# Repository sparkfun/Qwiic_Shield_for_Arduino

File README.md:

SparkFun Qwiic Shield for Arduino
========================================

[*SparkFun Qwiic Shield (DEV-14352)*](https://www.sparkfun.com/products/14352)

An Arduino shield to connect the I<sup>2</sup>C bus to 4 Qwiic connect ports.

Repository Contents
-------------------

* **/Hardware** - Eagle design files (.brd, .sch)

Documentation
--------------

* **[Hookup Guide](https://learn.sparkfun.com/tutorials/qwiic-shield-for-arduino--photon-hookup-guide)** - Basic hookup guide for the Arduino Qwiic Shield
* **[SparkFun Fritzing repo](https://github.com/sparkfun/Fritzing_Parts)** - Fritzing diagrams for SparkFun products.
* **[SparkFun 3D Model repo](https://github.com/sparkfun/3D_Models)** - 3D models of SparkFun products. 
* **[SparkFun Graphical Datasheets](https://github.com/sparkfun/Graphical_Datasheets)** -Graphical Datasheets for various SparkFun products.

Product Versions
----------------
* [DEV-14352](https://www.sparkfun.com/products/14352)- An Arduino shield to connect the I<sup>2</sup>C bus to 4 Qwiic connect ports.

Version History
---------------
* [V1.0.0](https://github.com/sparkfun/Qwiic_Shield_for_Arduino/releases/tag/V_1.0.0) - Initial Release

License Information
-------------------

This product is _**open source**_! 

Please review the LICENSE.md file for license information. 

If you have any questions or concerns on licensing, please contact techsupport@sparkfun.com.

Distributed as-is; no warranty is given.

- Your friends at SparkFun.

_<COLLABORATION CREDIT>_

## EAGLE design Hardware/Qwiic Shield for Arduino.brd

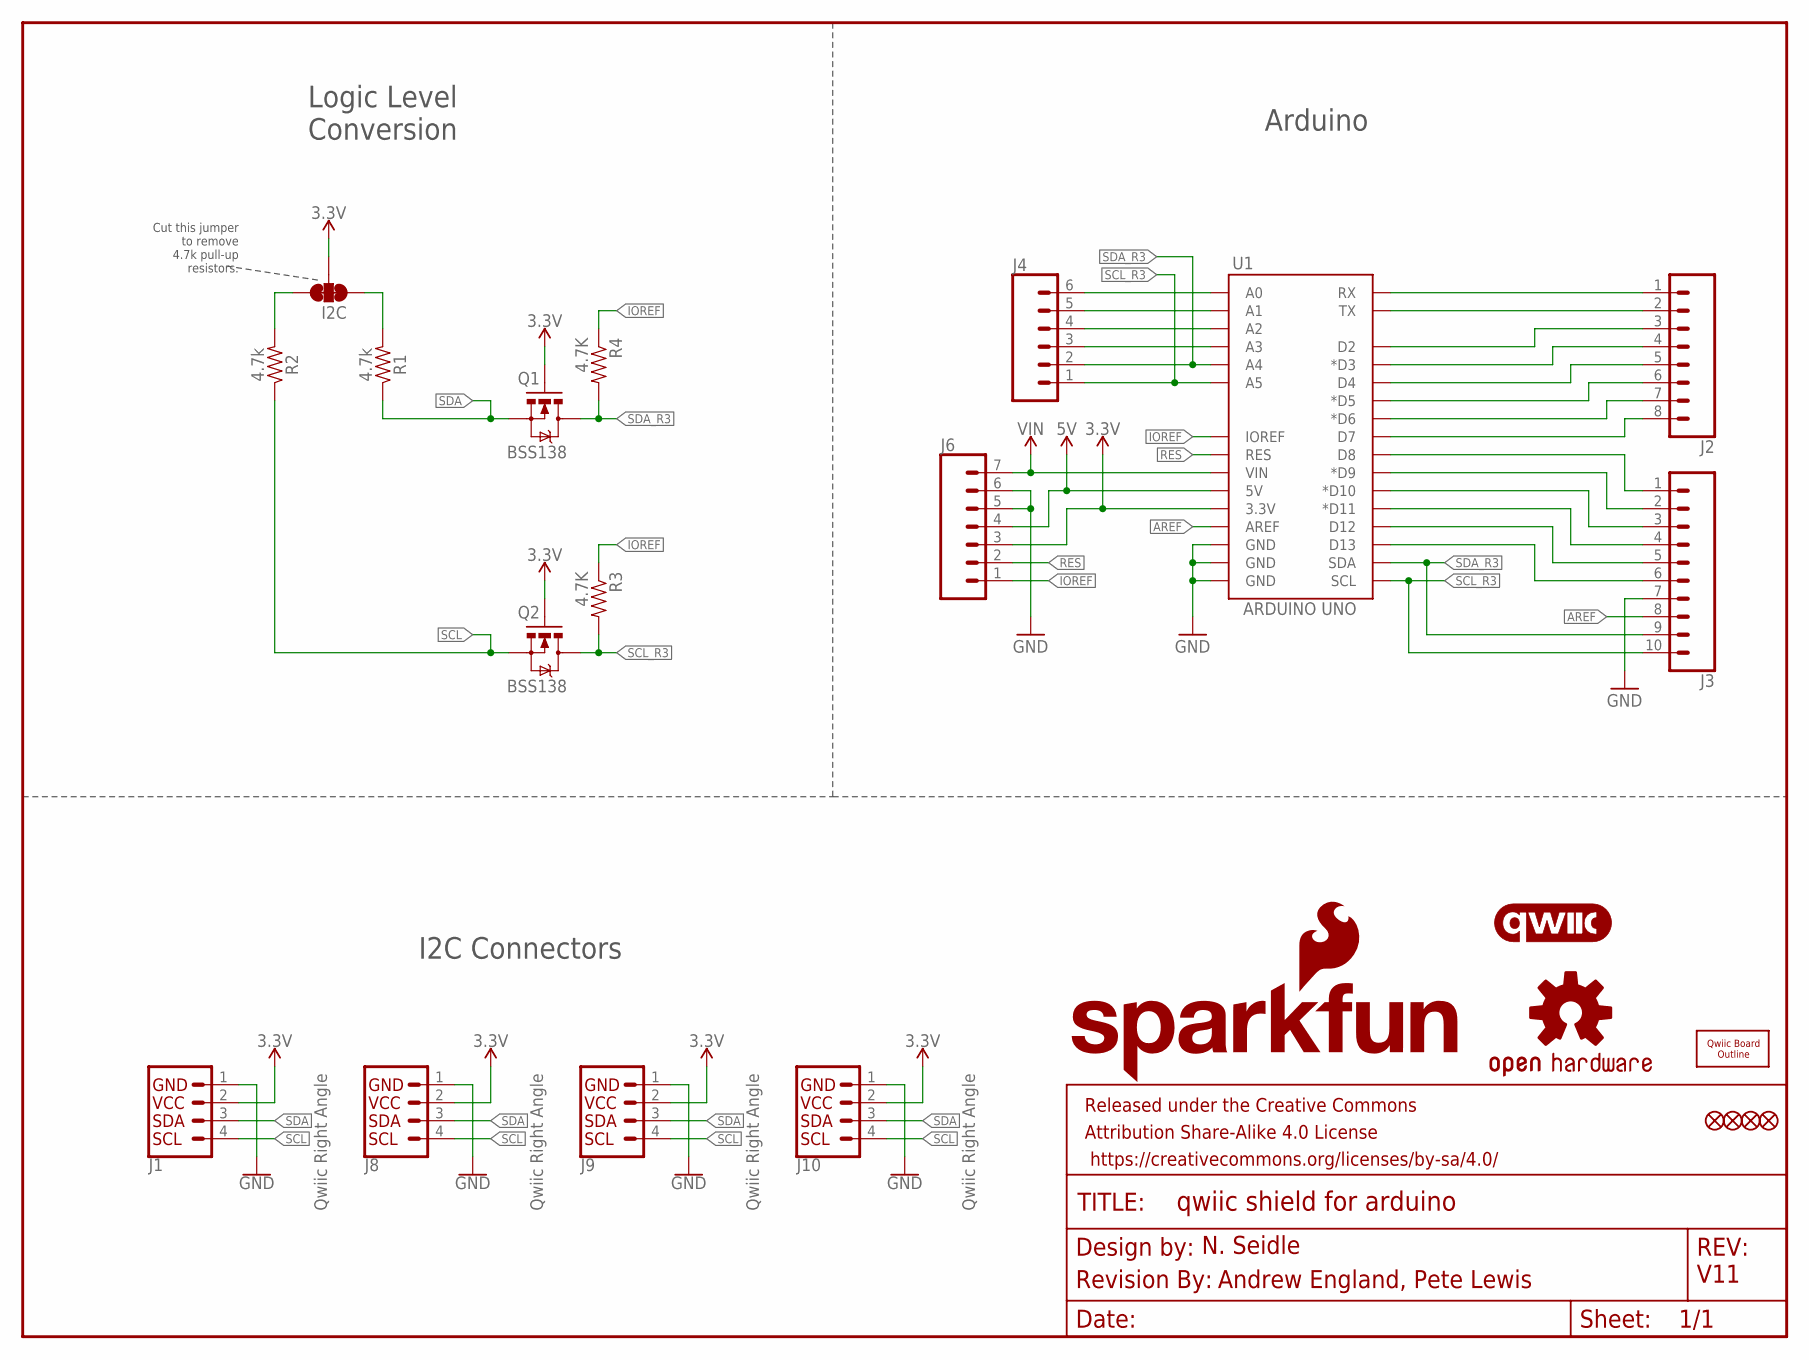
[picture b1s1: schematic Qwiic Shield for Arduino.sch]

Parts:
FD1, FD2, FD3, FD4: FIDUCIAL1X2; FIDUCIAL-1X2
FRAME1: FRAME-LETTER; CREATIVE_COMMONS
I2C: JUMPER-SMT_3_2-NC_TRACE_SILK; SMT-JUMPER_3_2-NC_TRACE_SILK
J1, J8, J9, J10: Qwiic Right Angle; 1X04_1MM_RA
J2: CONN_08NO_SILK_FEMALE_PTH; 1X08_NO_SILK
J3: CONN_10NO_SILK_PTH_FEMALE; 1X10_NO_SILK
J4: CONN_06NO_SILK_FEMALE_PTH; 1X06_NO_SILK
J6: CONN_07NO_SILK; 1X07_NO_SILK
LOGO1: OSHW-LOGOMINI; OSHW-LOGO-MINI
LOGO2: REVISION
LOGO3: QWIIC_LOGO_6MM; QWIIC_6MM
Q1, Q2: BSS138; SOT23-3
R1, R2: 4.7k; 0603
R3, R4: 4.7K; 0603-RES
U1: ARDUINO UNO; UNO_R3_SHIELD_NOLABELS
U$2: SFE_LOGO_NAME_FLAME.1_INCH; SFE_LOGO_NAME_FLAME_.1
U$3: QWIIC_BOARD_OUTLINEH; QWIIC_BOARD_MOUNT_HOLES

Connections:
3.3V: I2C.2, J1.2, J6.3, J8.2, J9.2, J10.2, Q1.1 (G), Q2.1 (G), U1.3.3V
5V: J6.4, U1.5V
A0: J4.6, U1.A0
A1: J4.5, U1.A1
A2: J4.4, U1.A2
A3: J4.3, U1.A3
AREF: J3.8, U1.AREF
D2: J2.3, U1.D2
D3: J2.4, U1.D3 (*D3)
D4: J2.5, U1.D4
D5: J2.6, U1.D5 (*D5)
D6: J2.7, U1.D6 (*D6)
D7: J2.8, U1.D7
D8: J3.1, U1.D8
D9: J3.2, U1.D9 (*D9)
D10: J3.3, U1.D10 (*D10)
D11: J3.4, U1.D11 (*D11)
D12: J3.5, U1.D12
D13: J3.6, U1.D13
GND: J1.1, J3.7, J6.5, J6.6, J8.1, J9.1, J10.1, U1.GND@0 (GND), U1.GND@1 (GND), U1.GND@2 (GND)
IOREF: J6.1, R3.1, R4.1, U1.IOREF
unnamed: I2C.3, R1.2
unnamed: I2C.1, R2.2
RES: J6.2, U1.RES
RX: J2.1, U1.RX
SCL: J1.4, J8.4, J9.4, J10.4, Q2.2 (S), R2.1
SCL_R3: J3.10, J4.1, Q2.3 (D), R3.2, U1.A5, U1.SCL
SDA: J1.3, J8.3, J9.3, J10.3, Q1.2 (S), R1.1
SDA_R3: J3.9, J4.2, Q1.3 (D), R4.2, U1.A4, U1.SDA
TX: J2.2, U1.TX
VIN: J6.7, U1.VIN

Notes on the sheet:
N. Seidle
Logic Level Conversion
Arduino
V11
I2C Connectors
Andrew England, Pete Lewis
Cut this jumper to remove 4.7k pull-up resistors.

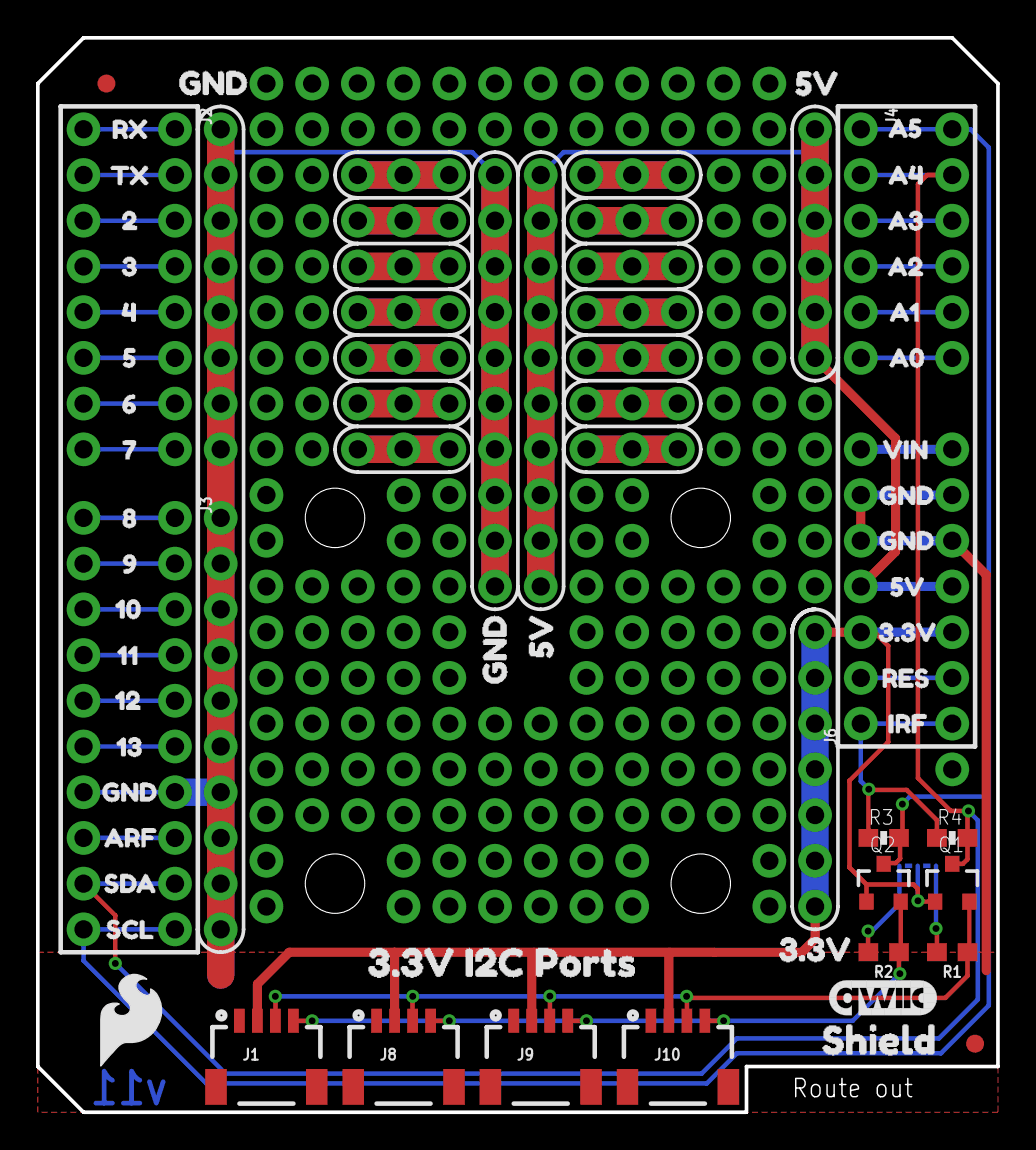
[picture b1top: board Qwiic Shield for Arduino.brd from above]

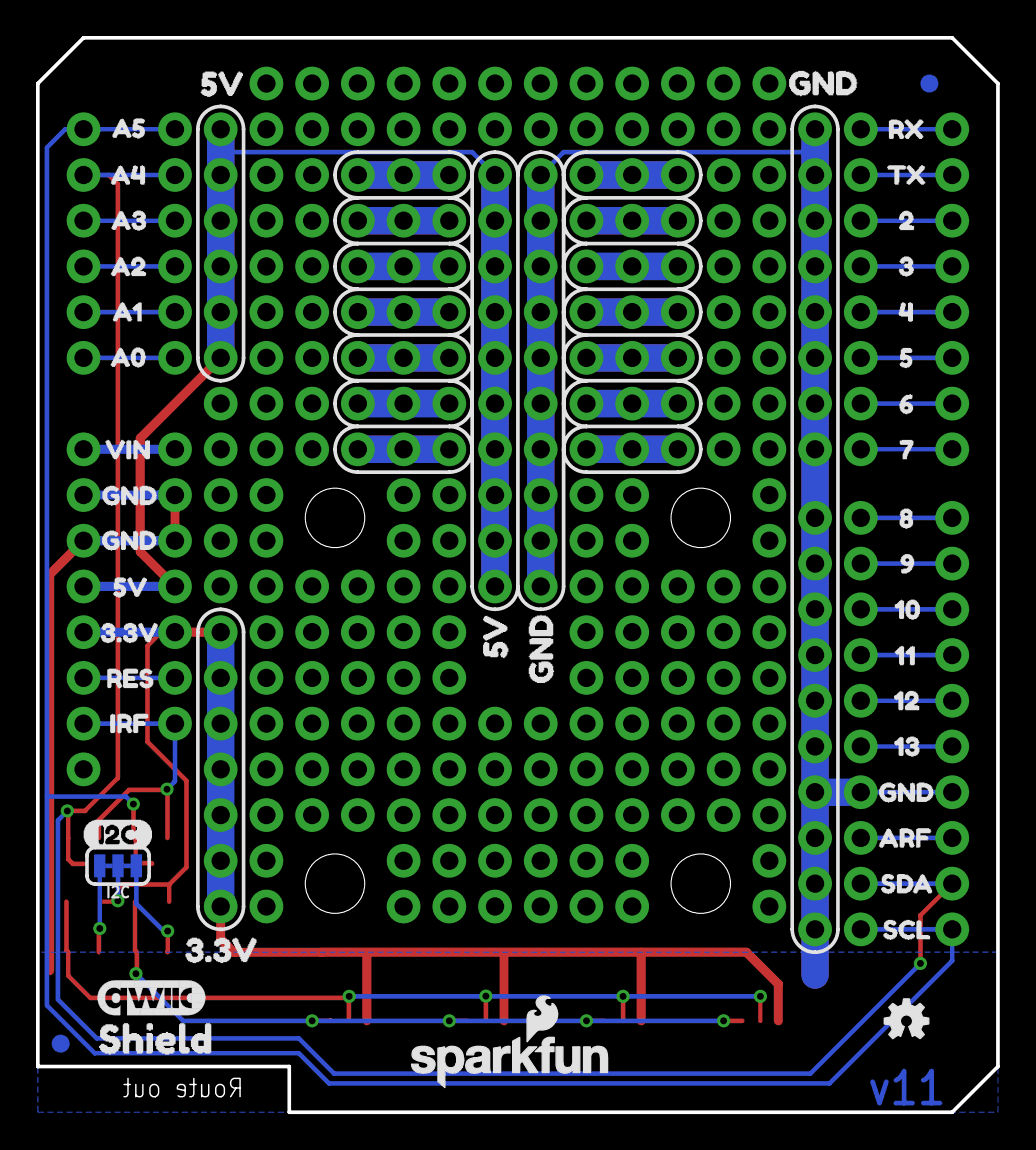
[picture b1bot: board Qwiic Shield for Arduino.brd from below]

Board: 2 copper layers, 53.3 x 59.7 mm, 104 parts (44 on the bottom side), 31 nets.

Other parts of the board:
LOGO4: QWIIC_LOGO_6MM; QWIIC_6MM
U$1: SFE_LOGO_FLAME_.2
U$4, U$5: SHIELD0
U$6: 3#3V_I2C_PORTS1
U$7, U$8: RX5
U$9, U$10: TX6
U$11, U$12: 27
U$13, U$14: 38
U$15, U$16: 49
U$17, U$18: 510
U$19, U$20: 611
U$21, U$23: 712
U$22: I2C0
U$24, U$25: 813
U$26, U$27: 914
U$28, U$29: 1015
U$30, U$31: 1116
U$32, U$33: 1217
U$34, U$35: 1318
U$36, U$37, U$68, U$69, U$70, U$71: GND30
U$38, U$39: ARF20
U$40, U$41: SDA21
U$42, U$43: SCL22
U$44, U$45, U$46, U$47: GND2
U$48, U$49: 3#3V4
U$50, U$51, U$52, U$53: 5V3
U$54, U$55: A523
U$56, U$57: A424
U$58, U$59: A325
U$60, U$61: A226
U$62, U$63: A127
U$64, U$65: A028
U$66, U$67: VIN29
U$72, U$73: 5V31
U$74, U$75: 3#3V32
U$76, U$77: RES33
U$78, U$79: IRF34

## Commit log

2017-06-16 added eagle files
2017-06-19 Updated readme, .gitignore, etc...
2017-06-20 Updated file structure to match SFE repo
2017-06-20 Changed over to Sparkfun library from SparkX
2017-07-10 Partially completed checklist, changes still need to be made
2017-07-17 Completed checklist + pre-design review changes
2017-07-17 Added mask and silk outline to rails. Added 3.3V Rail
2017-07-18 added units
2017-07-18 Added flame
2017-07-25 changed version number
2017-08-07 fixed aesthetic issues with power rails
2017-08-14 Added notch for barrel jack
2017-08-14 Post Design review changes
2017-08-18 Fixed route out in lower right corner
2017-08-23 Moved engineering checklist
2017-10-18 Initial Release
2017-10-18 fixed readme
2019-10-29 Connected R3 SDA/SCL pins and IOREF
    -SDA and SCL are now connected to both A4 /A5 pins and SDA/SCL pins.
    -Changed "high" logic side of converters to IOREF, to allow the Arduino to supply it's own IOREF. This will allow the shield to work with 3.3V logic Arduinos.
    -named PTH headers in the row of 3.3V to avoid overlap DRC errors.
    bumped version to v11 insch and brd
    - Added I2C pullup jumper to bottom side with label
    - rerouted SDA/SCL to allow for better GND return in pour
2019-10-29 Moved resistors to original location to maintain stencil spacing
2019-10-29 Moved qwiic board to SFE library
2019-10-29 net flags
2019-10-29 moved via away from qwiic silk logo

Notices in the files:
parts and their libraries:
SparkFun-Boards: Licensing: CC v3.0 Share-Alike You are welcome to use this library for commercial purposes.
SparkFun-Aesthetics: Released under the Creative Commons Attribution Share-Alike 4.0 License
SparkFun-Aesthetics: https://creativecommons.org/licenses/by-sa/4.0
